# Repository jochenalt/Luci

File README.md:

# Luci
A Lamp Robot like in the Pixar movies

This is the source of the lamp robot as shown in https://www.youtube.com/watch?v=dPnp3uZqJPc

### Contents
    /documentation	an article issued in the ODROID magazine describing the making-of
    /schematics		the schematics of the PBC controlled by an ODROID U3
    /CAD			TurboCAD files with hinges and lamp shade

    /sources						
    /sources/ATMegaSubController 	C++ code running on base of Arduino library
                                    controlling servos 
    /sources/LinuxMainController	C++ code running under Ubuntu/Odroid doing
                                    face recognition and trajectory planning
    /sources/Arduino 	            Copy of Arduino library used

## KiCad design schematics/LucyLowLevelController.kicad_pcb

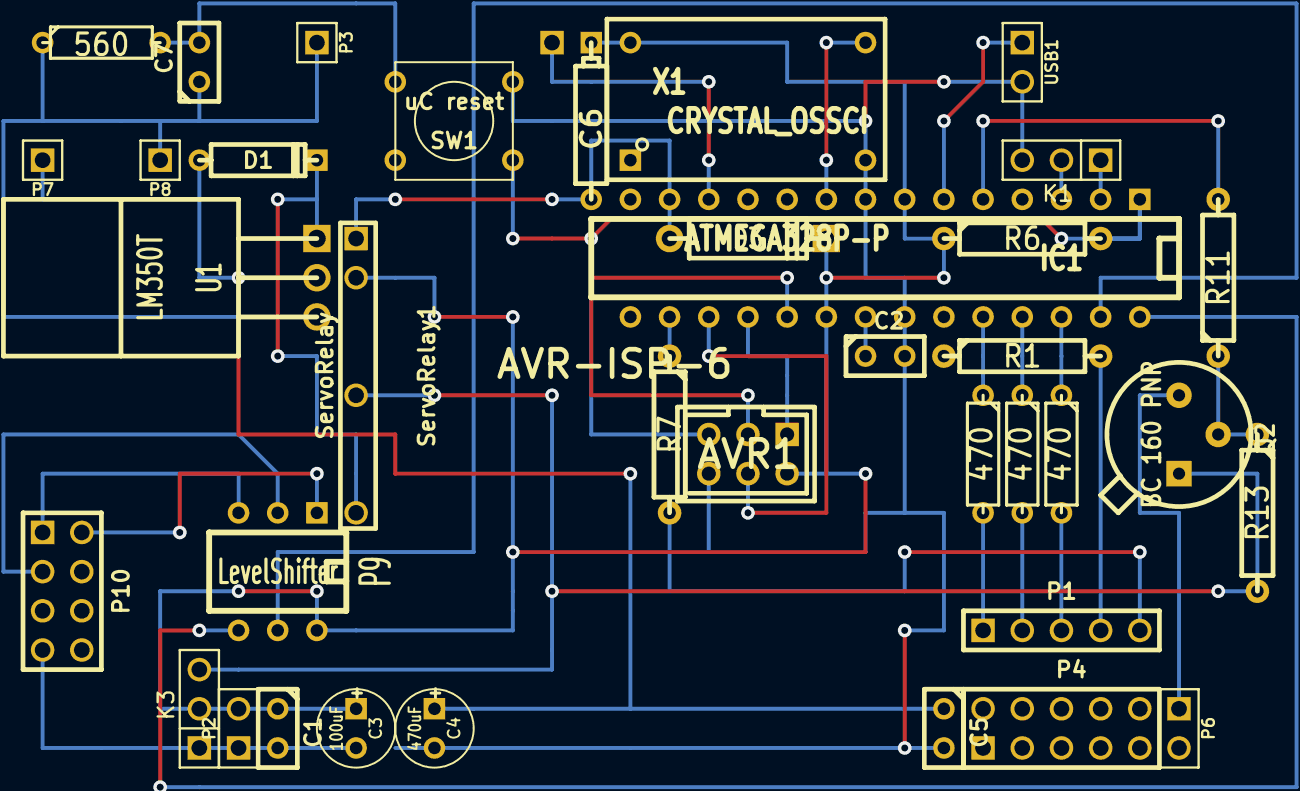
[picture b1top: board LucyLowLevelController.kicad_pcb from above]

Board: 2 copper layers, 38 parts (1 on the bottom side), 35 nets.

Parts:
AVR1: AVR-ISP-6
C1, C2, C5: 100nF; C1
C3: 100uF; C1V5
C4: 470uF; C1V5
C6: 1uF; CP4
C7: 1uF; C1
D1: DIODE; D3
D3: DIODE; D4
IC1: ATMEGA328P-P; DIP-28__300
K1: Serial Interface Connector; PIN_ARRAY_3X1
K3: Power IN; PIN_ARRAY_3X1
P1: Servo PWM; PIN_ARRAY_5x1
P2: Power Out ODROID; PIN_ARRAY_2X1
P3, P5, P7, P8: CONN_1; PIN_ARRAY_1
P4: Servo Block; PIN_ARRAY_5x2
P6: LED_CONN; PIN_ARRAY_2X1
P9: LevelShifter; DIP-6__300
P10: CONN_4X2; pin_array_4x2
Q2: BC 160 PNP; TO39EBC
R1, R7: 470; R4
R2, R3, R4: 470; R3
R6: 10K; R4
R10: 560; R3
R11: 860; R4
R13: 220; R4
SW1: uC reset; SW_PUSH_SMALL
ServoRelay1: ServoRelay; Slimline-Relay-HF49FD
U1: LM350T; TO220_VOLTAGE_REGUL_ADJ
USB1: LED_CONN; PIN_ARRAY_2X1
X1: CRYSTAL_OSSCI; QUARTZ_OSCILLATOR_DIL14

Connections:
+5V: AVR1.2, C1.1, C3.1, C6.1, D3.2, IC1.7, IC1.20, K3.2, P2.2, P9.6, R6.1, ServoRelay1.3, X1.14
/1.8V: P9.1, P10.2
/#199: P9.3, P10.1
/#200: P9.2, P10.3
/+8V: K3.3, Q2.1, R13.2, ServoRelay1.5
/GND: AVR1.6, C1.2, C2.2, C3.2, C4.2, C5.2, C7.2, IC1.8, IC1.22, K1.3, K3.1, P2.1, P4.1, P4.3, P4.5, P4.7, P4.9, P6.2, P10.7, R10.2, SW1.2, USB1.2, X1.7
/MISO: AVR1.1, IC1.18
/MOSI: AVR1.4, IC1.17
/RST: AVR1.5, IC1.1, R6.2, SW1.1
/RX: IC1.2, K1.1
/Relay-: C6.2, D3.1, IC1.13, ServoRelay1.1
/SCK: AVR1.3, IC1.19
/SCL: IC1.28, P9.4
/SDA: IC1.27, P9.5
/Servo1: P1.5, R7.2
/Servo2: P1.4, R1.2
/Servo3: P1.1, R2.2
/Servo4: P1.2, R3.2
/Servo5: P1.3, R4.2
/Startup: IC1.12, P5.1
/TX: IC1.3, K1.2
unnamed: C2.1, IC1.21
unnamed: C4.1, C5.1, D1.1, P4.2, P4.4, P4.6, P4.8, P4.10, P7.1, U1.2
unnamed: C7.1, P3.1, P8.1, R10.1, U1.1
unnamed: D1.2, U1.3
unnamed: IC1.5, R11.2
unnamed: IC1.6, USB1.1
unnamed: IC1.9, X1.8
unnamed: IC1.16, R7.1
unnamed: IC1.23, R1.1
unnamed: IC1.24, R2.1
unnamed: IC1.25, R3.1
unnamed: IC1.26, R4.1
unnamed: P6.1, Q2.3
unnamed: Q2.2, R11.1, R13.1

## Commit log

2015-08-14 Added schematics and CAD files
2015-08-14 added Arduino code
2015-08-14 added documentation
2015-08-14 ODROID Magazine Article
2015-08-15 Added ODROID code
2015-08-15 lost&found
2015-08-19 cleaned up code
2019-05-23 Update makefile
